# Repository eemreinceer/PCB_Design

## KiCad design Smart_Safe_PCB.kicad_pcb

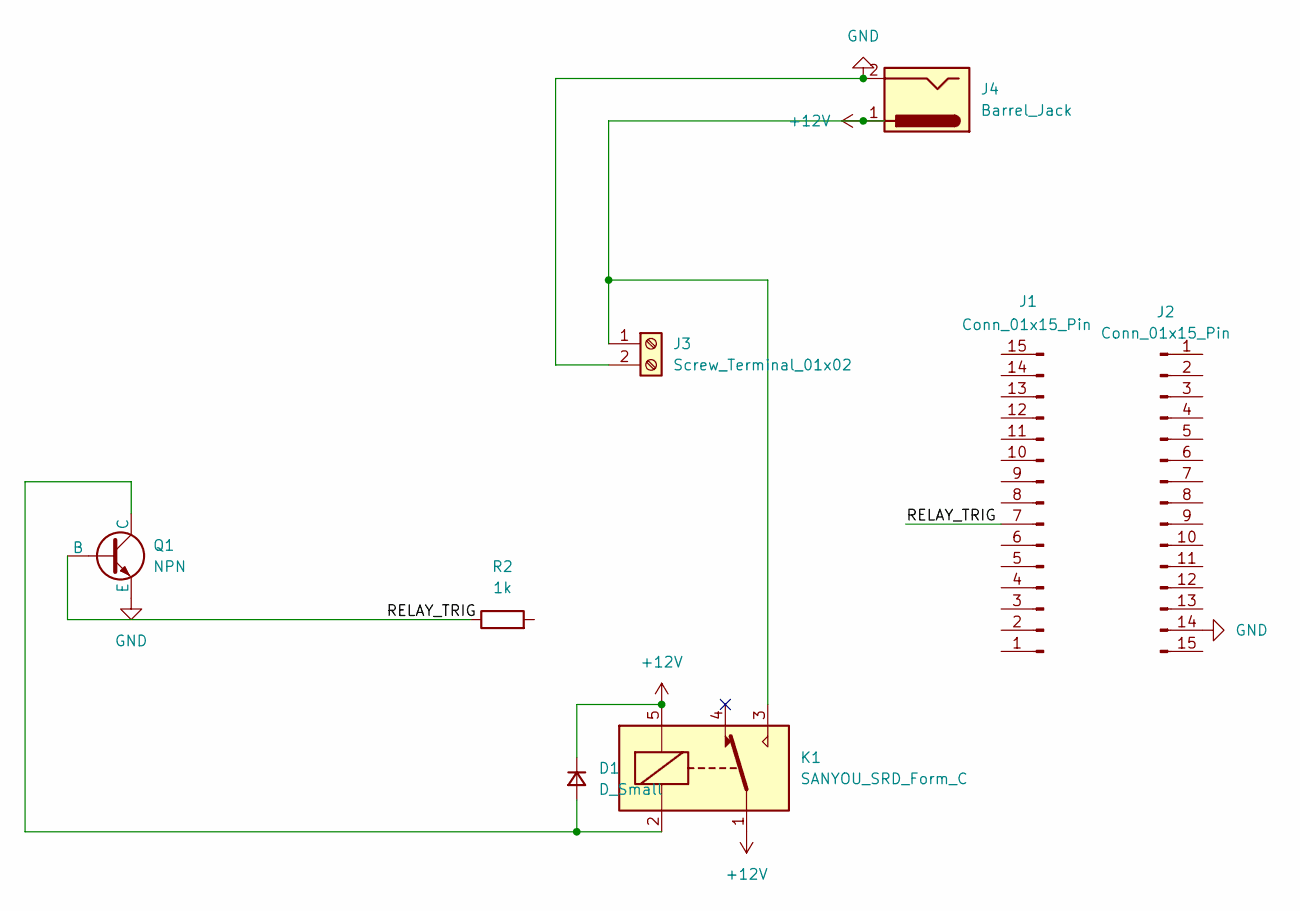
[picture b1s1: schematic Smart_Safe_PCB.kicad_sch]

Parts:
D1: D_Small; D_DO-41_SOD81_P10.16mm_Horizontal
J1, J2: Conn_01x15_Pin; PinHeader_1x15_P2.54mm_Vertical
J3: Screw_Terminal_01x02; TerminalBlock_Phoenix_MKDS-1,5-2-5.08_1x02_P5.08mm_Horizont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
J4: Barrel_Jack; TerminalBlock_Phoenix_MKDS-1,5-2-5.08_1x02_P5.08mm_Horizont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
K1: SANYOU_SRD_Form_C; Relay_SPDT_SANYOU_SRD_Series_Form_C
Q1: NPN; TO-92_Inline
R2: 1k; R_Axial_DIN0207_L6.3mm_D2.5mm_P7.62mm_Horizontal

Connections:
+12V: D1.1 (K), J3.1, J4.1, K1.1, K1.3, K1.5
/RELAY_TRIG: J1.7, Q1.2 (B), R2.1
GND: J2.14, J3.2, J4.2, Q1.3 (E)
unnamed: D1.2 (A), K1.2, Q1.1 (C)

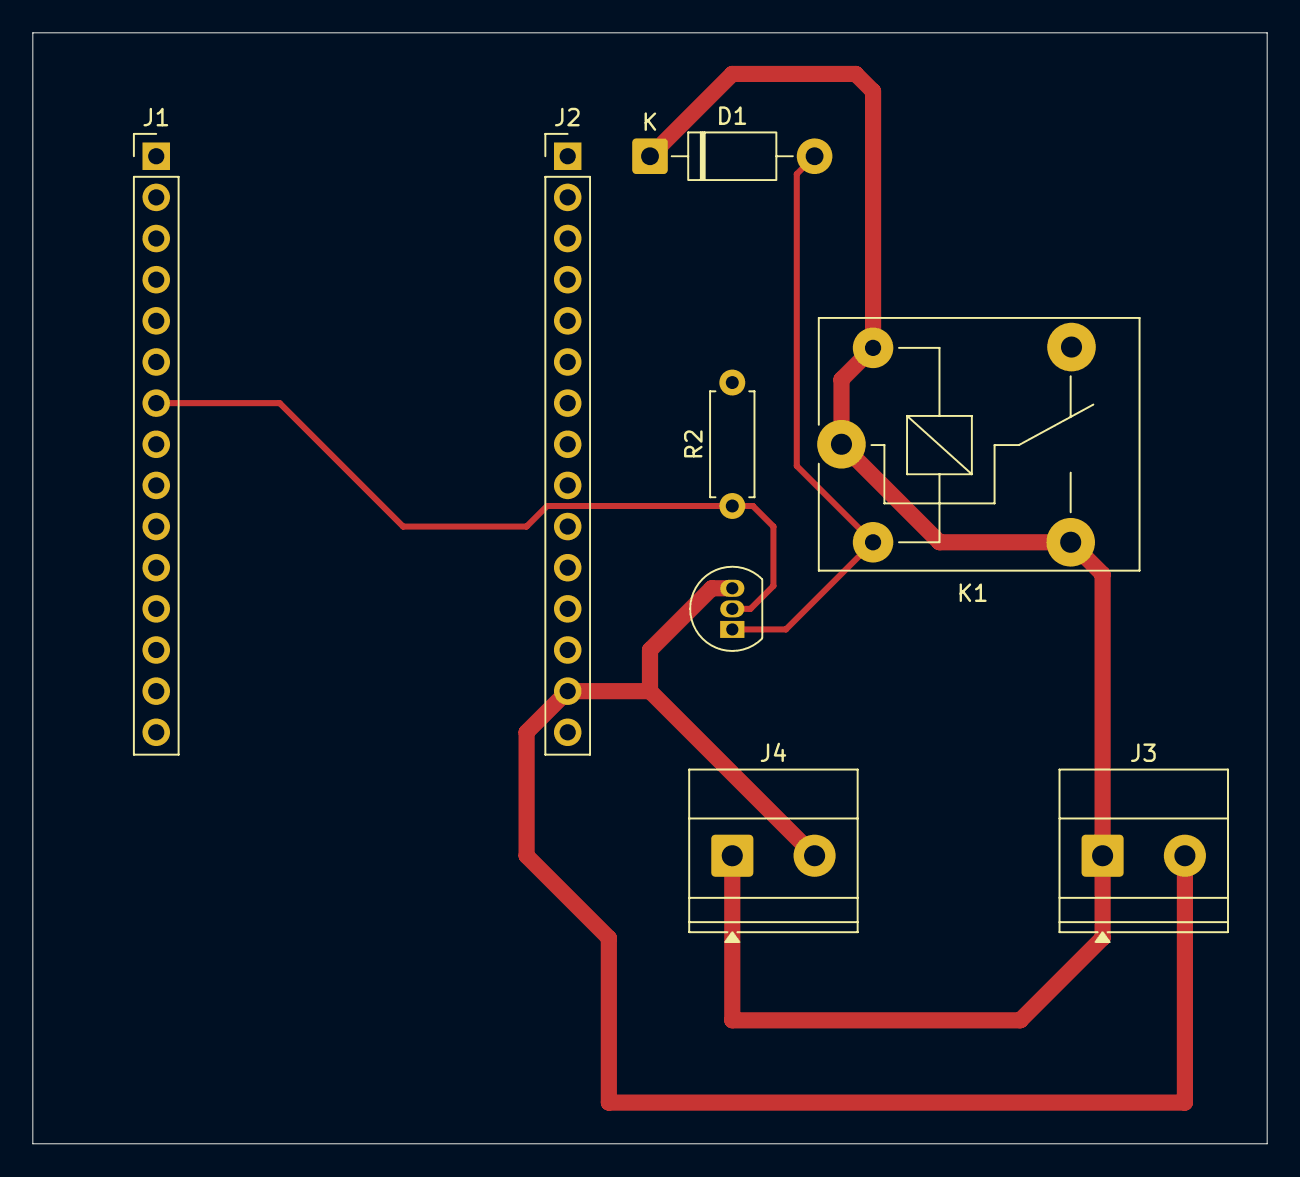
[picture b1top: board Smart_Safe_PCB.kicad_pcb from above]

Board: 2 copper layers, 76.2 x 68.6 mm, 8 parts (0 on the bottom side), 4 nets.
